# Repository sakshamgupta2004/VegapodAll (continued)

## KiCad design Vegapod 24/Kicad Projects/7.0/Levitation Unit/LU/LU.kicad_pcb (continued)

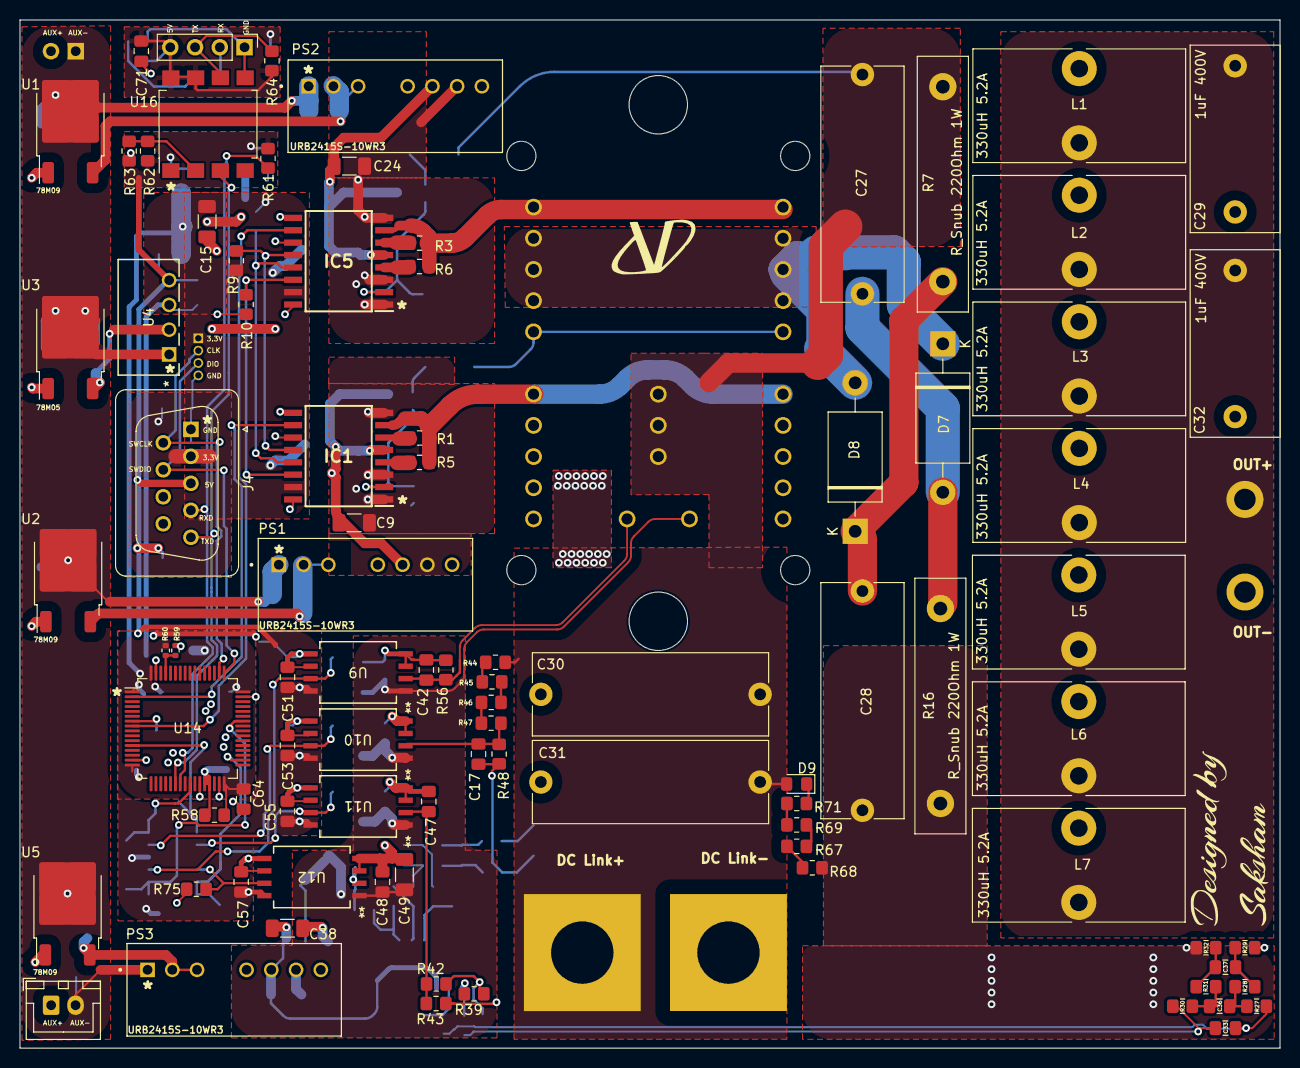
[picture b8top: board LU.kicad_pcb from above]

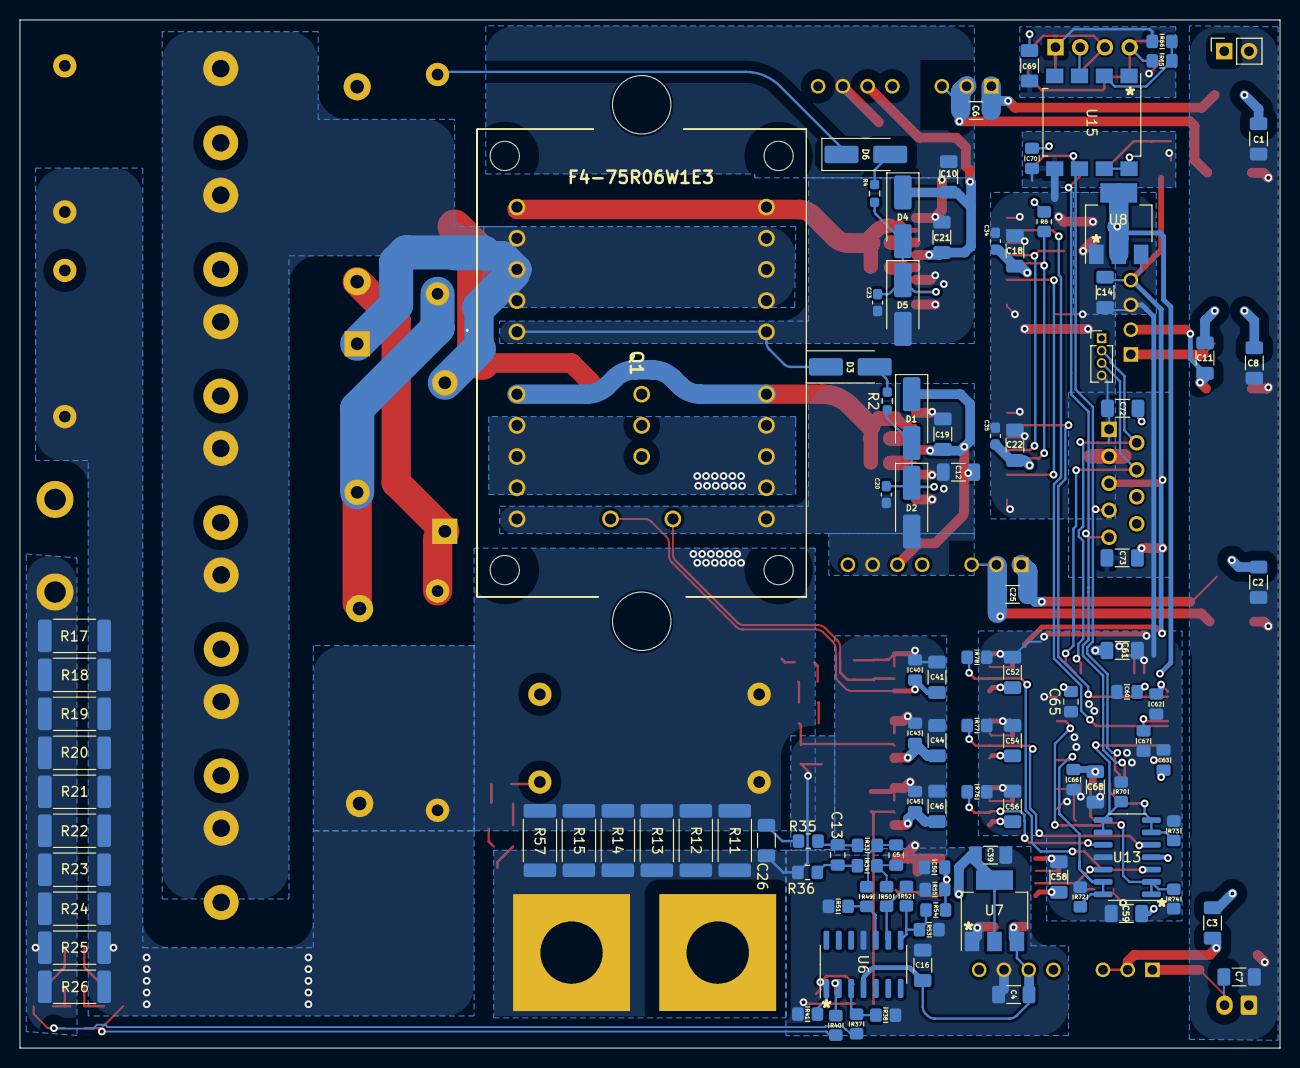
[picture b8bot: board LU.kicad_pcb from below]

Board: 2 copper layers, 129.3 x 105.5 mm, 198 parts (106 on the bottom side), 86 nets.

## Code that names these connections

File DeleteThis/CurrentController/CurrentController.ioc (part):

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Mcu.Name=STM32G474R(B-C-E)Tx
Mcu.Package=LQFP64
Mcu.UserName=STM32G474RETx
PA0.Mode=IN1-Single-Ended
PA0.Signal=ADC1_IN1
PA13.Mode=Serial_Wire
PA13.Signal=SYS_JTMS-SWDIO
PA14.Mode=Serial_Wire
PA14.Signal=SYS_JTCK-SWCLK
PA3.Signal=GPIO_Input
PA4.Mode=NSS_Signal_Hard_Input
PA4.Signal=SPI1_NSS
PA5.Mode=Full_Duplex_Slave
PA5.Signal=SPI1_SCK
PA6.Mode=Full_Duplex_Slave
PA6.Signal=SPI1_MISO
PA7.Mode=Full_Duplex_Slave
PA7.Signal=SPI1_MOSI
PA8.Signal=GPIO_Output
PB1.Mode=IN1-Single-Ended
PB1.Signal=ADC3_IN1
PC4.Mode=Asynchronous
PC4.Signal=USART1_TX
PC5.Mode=Asynchronous
PC5.Signal=USART1_RX
PC8.Signal=GPIO_Output
PC9.Signal=GPIO_Output
PF0-OSC_IN.Mode=HSE-External-Oscillator
PF0-OSC_IN.Signal=RCC_OSC_IN
PF1-OSC_OUT.Mode=HSE-External-Oscillator
PF1-OSC_OUT.Signal=RCC_OSC_OUT
RCC.HSE_VALUE=8000000
RCC.SYSCLKFreq_VALUE=170000000
RCC.SYSCLKSource=RCC_SYSCLKSOURCE_PLLCLK
board=custom

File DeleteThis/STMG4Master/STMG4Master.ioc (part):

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Mcu.Name=STM32G474R(B-C-E)Tx
Mcu.Package=LQFP64
Mcu.UserName=STM32G474RETx
PA0.Mode=IN1-Single-Ended
PA0.Signal=ADC1_IN1
PA8.Signal=GPIO_Output
PB1.Mode=IN1-Single-Ended
PB1.Signal=ADC3_IN1
PB2.Signal=GPIO_Input
PB3.Signal=GPIO_Input
PC4.Mode=Asynchronous
PC4.Signal=USART1_TX
PC5.Mode=Asynchronous
PC5.Signal=USART1_RX
PC8.Signal=GPIO_Output
PC9.Signal=GPIO_Output
RCC.HSE_VALUE=16000000
RCC.SYSCLKFreq_VALUE=170000000
RCC.SYSCLKSource=RCC_SYSCLKSOURCE_PLLCLK
board=custom

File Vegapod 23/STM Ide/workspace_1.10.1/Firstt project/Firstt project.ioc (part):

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Mcu.Name=STM32F302R(6-8)Tx
Mcu.Package=LQFP64
Mcu.UserName=STM32F302R8Tx
PA13.GPIOParameters=GPIO_Label
PA13.GPIO_Label=TMS
PA13.Signal=SYS_JTMS-SWDIO
PA14.GPIOParameters=GPIO_Label
PA14.GPIO_Label=TCK
PA14.Signal=SYS_JTCK-SWCLK
PA2.GPIOParameters=GPIO_Speed,GPIO_PuPd,GPIO_Label,GPIO_Mode
PA2.GPIO_Label=USART_TX
PA2.GPIO_Mode=GPIO_MODE_AF_PP
PA2.GPIO_PuPd=GPIO_NOPULL
PA2.GPIO_Speed=GPIO_SPEED_FREQ_LOW
PA2.Signal=USART2_TX
PA3.GPIOParameters=GPIO_Speed,GPIO_PuPd,GPIO_Label,GPIO_Mode
PA3.GPIO_Label=USART_RX
PA3.GPIO_Mode=GPIO_MODE_AF_PP
PA3.GPIO_PuPd=GPIO_NOPULL
PA3.GPIO_Speed=GPIO_SPEED_FREQ_LOW
PA3.Signal=USART2_RX
PB13.GPIOParameters=GPIO_Label
PB13.GPIO_Label=LD2 [Green Led]
PB13.Signal=GPIO_Output
PB3.GPIOParameters=GPIO_Label
PB3.GPIO_Label=SWO
PB3.Signal=SYS_JTDO-TRACESWO
PC13.GPIOParameters=GPIO_Label,GPIO_ModeDefaultEXTI
PC13.GPIO_Label=B1 [Blue PushButton]
PC13.GPIO_ModeDefaultEXTI=GPIO_MODE_IT_FALLING
PC13.Signal=GPXTI13
PC14\ -\ OSC32_IN.Signal=RCC_OSC32_IN
PC15\ -\ OSC32_OUT.Signal=RCC_OSC32_OUT
PF0-OSC_IN.Signal=RCC_OSC_IN
PF1-OSC_OUT.Signal=RCC_OSC_OUT
RCC.HSEPLLFreq_Value=4000000
RCC.HSE_VALUE=8000000
RCC.SYSCLKFreq_VALUE=64000000
RCC.SYSCLKSourceVirtual=RCC_SYSCLKSOURCE_PLLCLK
board=NUCLEO-F302R8
boardIOC=true

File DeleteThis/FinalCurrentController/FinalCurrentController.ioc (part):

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Mcu.Name=STM32G474R(B-C-E)Tx
Mcu.Package=LQFP64
Mcu.UserName=STM32G474RETx
PA0.Mode=IN1-Single-Ended
PA0.Signal=ADC1_IN1
PA8.Mode=IN1-Single-Ended
PA8.Signal=ADC5_IN1
PB1.Mode=IN1-Single-Ended
PB1.Signal=ADC3_IN1
PB12.Mode=IN3-Single-Ended
PB12.Signal=ADC4_IN3
PC0.Signal=S_TIM1_CH1
PC13.Mode=PWM Generation1 CH1 CH1N
PC13.Signal=TIM1_CH1N
PC4.Mode=Asynchronous
PC4.Signal=USART1_TX
PC5.Mode=Asynchronous
PC5.Signal=USART1_RX
RCC.HSE_VALUE=8000000
RCC.SYSCLKFreq_VALUE=170000000
RCC.SYSCLKSource=RCC_SYSCLKSOURCE_PLLCLK
board=custom

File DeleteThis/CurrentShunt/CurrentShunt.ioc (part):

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Mcu.Name=STM32F030F4Px
Mcu.Package=TSSOP20
Mcu.UserName=STM32F030F4Px
PA0.Mode=IN0
PA0.Signal=ADC_IN0
PA1.Mode=IN1
PA1.Signal=ADC_IN1
PA13.Mode=Serial_Wire
PA13.Signal=SYS_SWDIO
PA14.Mode=Serial_Wire
PA14.Signal=SYS_SWCLK
PA2.Mode=IN2
PA2.Signal=ADC_IN2
PA3.Mode=Asynchronous
PA3.Signal=USART1_RX
PA9.Mode=Asynchronous
PA9.Signal=USART1_TX
board=custom

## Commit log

2023-12-27 Made both PCBs that should function for BMS Slave
2024-01-03 Ordered pcbs for bms
2024-01-08 Inverter PCB Done
2024-01-13 IDEK
2024-01-13 Removed Backup files
2024-01-25 IDEK but LTC6804 Ordered
2024-01-26 Inverter 0 errors ready to export, LU fucked
2024-01-26 Inverter changes - power routing - incomplete
2024-01-28 Inverter gbr generated
2024-01-28 Inverter add dc link sense
2024-01-28 Sort shit and added readme.md
2024-01-28 added shit from all across pc (all vgp)
2024-01-28 Fixed Shit i broke in inverter pcb
2024-01-29 Sent gerber to aardra
2024-02-07 LU and PID Code in workspace
2024-02-13 LU Working ig
2024-02-15 Opamp BMS Slave print ig and some changes to stm code
2024-02-17 External trigger stm code, OPAMP BMS 1mm via
2024-02-17 Change to simulation
2024-02-17 Seperated boost converter and chg dschg controller
2024-02-18 Design of Chg Dschg controller ready
2024-02-20 just stm code
2024-02-22 Some code
2024-02-22 change gerber again
2024-02-22 changes to current controller
2024-02-26 Change code stm and generate pdf gerbers
2024-03-06 No changes really
2024-03-08 Half done LU for testing
2024-03-08 Moved to kicad 6.0 folder from wrong one
2024-03-11 diagram
2024-03-13 Added page info to schematic battery module
2024-03-14 Schematic rearrange bms slave
2024-03-15 Resize schematic battery module
2024-03-15 Levitation Power Module Block Diagram
2024-03-18 Cell Auto Discharging Balanced
2024-03-26 Almost complete bms slave
2024-03-29 LU PCB
2024-03-29 BMS PCB
2024-03-30 Power side complete lu
2024-04-02 Battery box pcbs done
2024-04-07 LU testing board
2024-04-07 BMS heatsink holes cad
2024-04-11 UART and stlink missing lu board
2024-04-12 LU Board Semi Final
2024-04-13 Val changes to lu test pcb
2024-04-16 ZIP BMS OPAMP
2024-04-16 Minorest change to bms sch
2024-05-04 nothing much changed values in sch
2024-05-14 Added boost converter
2024-05-31 Levitation Unit completed (review phase)
2024-05-31 Final touches to LU
2024-05-31 A lil simulation
2024-06-02 Precharge PCB for 2 contactors 200A
2024-06-03 Added IMD Support to interlock
2024-06-03 Added vegapod logo to Interlock
2024-06-05 BMS master pcb partial
2024-06-05 BMS Master completed
2024-06-05 Flyback diode for contactor
2024-06-05 Add boot pin conn. (forgor💀)
2024-06-18 LV BMS half
2024-06-20 BMS Master changes because fucked up
2024-06-20 BMS Master final changes
2024-06-21 Trying to make vegapod 25
2024-06-22 BMS LV Done probably
2024-06-22 Finding fault in blown lu
2025-01-19 IDK What changed . pretty much nothing
2025-02-18 Add Digital Current Shunt
2025-03-16 add current shunt gerbers
2025-03-16 added stm cube workspace
2025-03-19 Remove Workspace
2025-03-26 New BMS PCB started
2025-04-16 eidk
2025-11-14 Capstone project...
2025-12-24 Some inverter circuit
2025-12-26 Research Paper Inverter Test
2025-12-27 CADs
2026-01-11 BMS Plots
